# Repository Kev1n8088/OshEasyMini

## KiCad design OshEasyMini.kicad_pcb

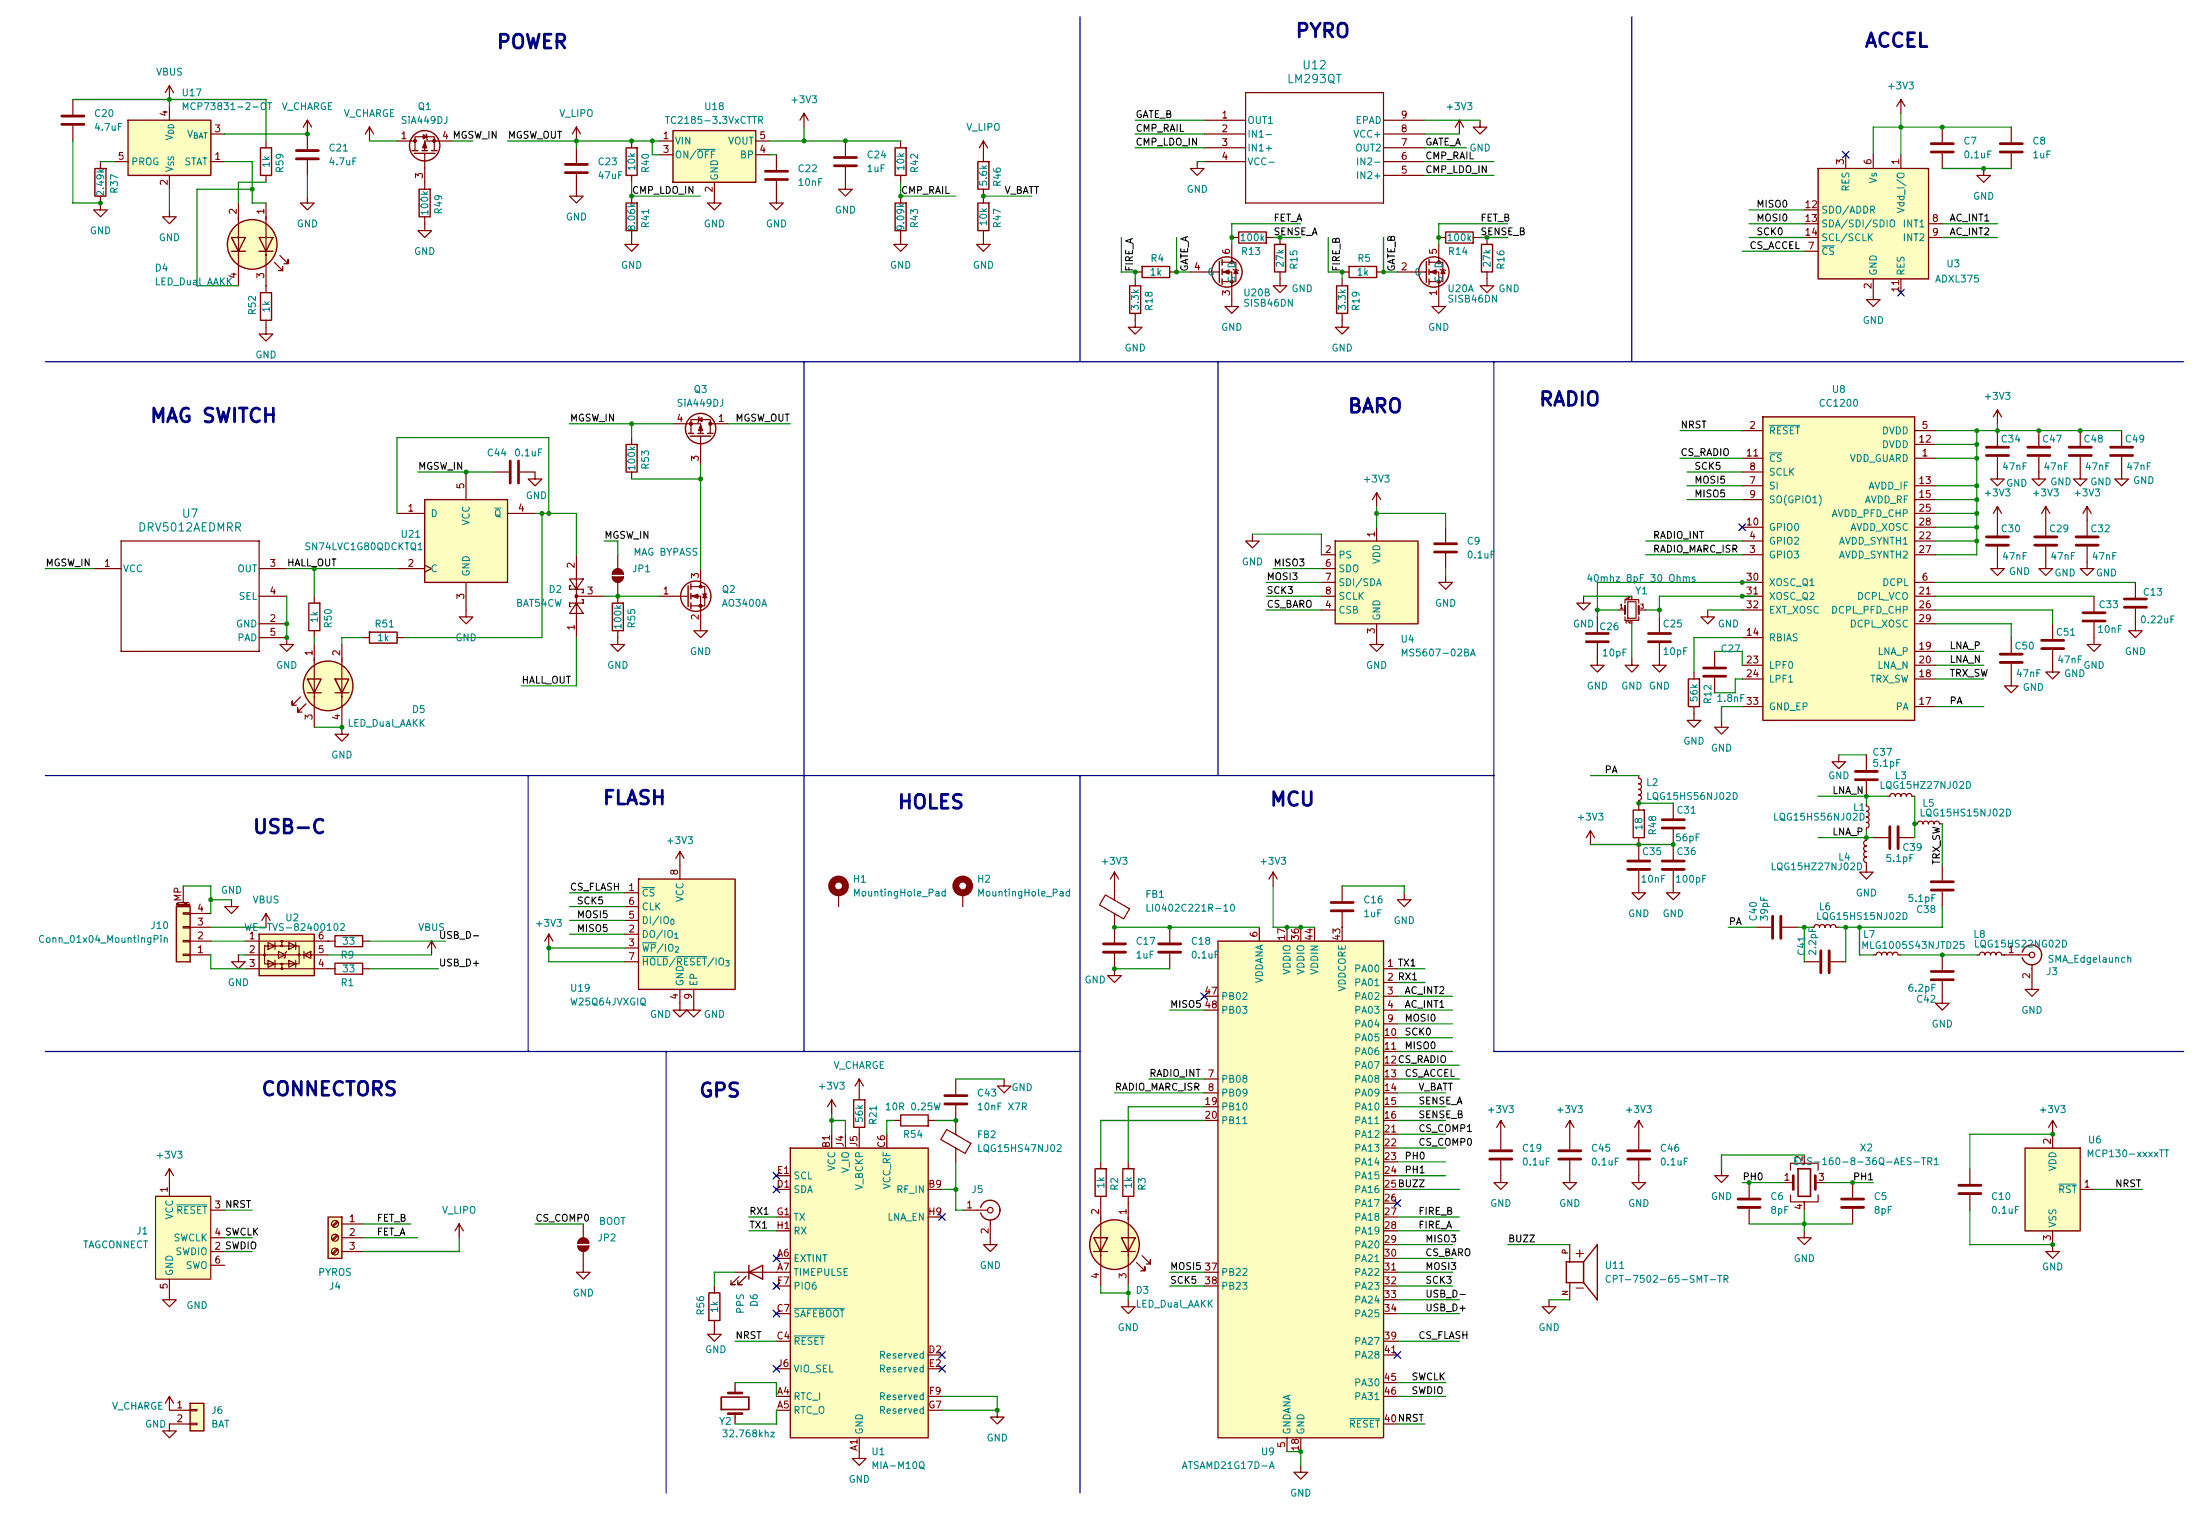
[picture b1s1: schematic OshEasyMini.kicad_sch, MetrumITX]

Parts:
C5, C6: 8pF; C_0402_1005Metric
C7, C9, C10, C18, C19, C44, C45, C46: 0.1uF; C_0402_1005Metric
C8, C16, C17, C24: 1uF; C_0402_1005Metric
C13: 0.22uF; C_0402_1005Metric
C20, C21: 4.7uF; C_0402_1005Metric
C22: 10nF; C_0201_0603Metric
C23: 47uF; C_1206_3216Metric
C25, C26: 10pF; C_0402_1005Metric
C27: 1.8nF; C_0402_1005Metric
C29, C30, C32, C34, C47, C48, C49, C50, C51: 47nF; C_0201_0603Metric
C31: 56pF; C_0402_1005Metric
C33, C35: 10nF; C_0402_1005Metric
C36: 100pF; C_0402_1005Metric
C37, C38, C39: 5.1pF; C_0402_1005Metric
C40: 39pF; C_0402_1005Metric
C41: 2.2pF; C_0402_1005Metric
C42: 6.2pF; C_0402_1005Metric
C43: 10nF X7R; C_0402_1005Metric
D2: BAT54CW; SOT-323_SC-70
D3, D4, D5: LED_Dual_AAKK; DualLED0606
D6: PPS; LED_0402_1005Metric
FB1: LI0402C221R-10; L_0402_1005Metric
FB2: LQG15HS47NJ02; L_0402_1005Metric
H1, H2: MountingHole_Pad; MountingHole_2.7mm_M2.5_DIN965_Pad
J1: TAGCONNECT; Tag-Connect_TC2030-IDC-NL_2x03_P1.27mm_Vertical
J3: SMA_Edgelaunch; SMA_Amphenol_132289_EdgeMount
J4: PYROS; TerminalBlock_Phoenix_MPT-0,5-3-2.54_1x03_P2.54mm_Horizontal
J5: UFL; U.FL_Molex_MCRF_73412-0110_Vertical
J6: BAT; JST_PH_B2B-PH-K_1x02_P2.00mm_Vertical
J10: Conn_01x04_MountingPin; JST_SH_BM04B-SRSS-TB_1x04-1MP_P1.00mm_Vertical
JP1: MAG BYPASS; SolderJumper-2_P1.3mm_Open_TrianglePad1.0x1.5mm
JP2: BOOT; SolderJumper-2_P1.3mm_Open_TrianglePad1.0x1.5mm
L1, L2: LQG15HS56NJ02D; L_0402_1005Metric
L3, L4: LQG15HZ27NJ02D; L_0402_1005Metric
L5, L6: LQG15HS15NJ02D; L_0402_1005Metric
L7: MLG1005S43NJTD25; L_0402_1005Metric
L8: LQG15HS22NG02D; L_0402_1005Metric
Q1, Q3: SiA449DJ; Vishay_PowerPAK_SC70-6L_Single
Q2: AO3400A; SOT-23
R1, R9: 33; R_0201_0603Metric
R2, R3, R4, R5, R50, R51, R52, R56, R59: 1k; R_0201_0603Metric
R12, R21: 56k; R_0402_1005Metric
R13, R14: 100k; R_0402_1005Metric
R15, R16: 27k; R_0402_1005Metric
R18, R19: 3.3k; R_0402_1005Metric
R37: 2.49k; R_0402_1005Metric
R40, R42, R47: 10k; R_0201_0603Metric
R41: 8.06k; R_0201_0603Metric
R43: 9.09k; R_0201_0603Metric
R46: 5.6k; R_0201_0603Metric
R48: 18; R_0402_1005Metric
R49, R53, R55: 100k; R_0201_0603Metric
R54: 10R 0.25W; R_0402_1005Metric
U1: MIA-M10Q; ublox_LGA-53_4.5x4.5mm_Layout9x9_P0.5mm
U2: WE-TVS-82400102; SOT-23-6
U3: ADXL375; LGA-14_3x5mm_P0.8mm_LayoutBorder1x6y
U4: MS5607-02BA; LGA-8_3x5mm_P1.25mm
U6: MCP130-xxxxTT; SOT-23
U7: DRV5012AEDMRR; Texas_X2SON-4-1EP_1.1x1.4mm_P0.5mm_EP0.8x0.6mm
U8: CC1200; QFN-32-1EP_5x5mm_P0.5mm_EP3.45x3.45mm
U9: ATSAMD21G17D-A; TQFP-48_7x7mm_P0.5mm
U11: CPT-7502-65-SMT-TR; XDCR_CPT-7502-65-SMT-TR; PARTREV 1.0
U12: LM293QT; DFN-8-1EP_2x2mm_P0.5mm_EP0.9x1.6mm
U17: MCP73831-2-OT; SOT-23-5
U18: TC2185-3.3VxCTTR; SOT-23-5
U19: W25Q64JVXGIQ; DFN_XGIQ TR_WIN
U20: SISB46DN; PowerPak1212-8-Dual
U21: SN74LVC1G80QDCKTQ1; SOT-353_SC-70-5
X2: ECS-160-8-36Q-AES-TR1; Crystal_SMD_2520-4Pin_2.5x2.0mm
Y1: 40mhz 8pF 30 Ohms; Crystal_SMD_Abracon_ABM10-4Pin_2.5x2.0mm
Y2: 32.768khz; Crystal_SMD_MicroCrystal_CM9V-T1A-2Pin_1.6x1.0mm

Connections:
+3V3: C7.2, C8.2, C9.2, C10.2, C19.2, C24.2, C29.2, C30.2, C31.1, C32.2, C34.2, C35.2, C36.2, C45.2, C46.2, C47.2, C48.2, C49.2, FB1.2, J1.1 (VCC), R42.2, R48.1, U1.B1 (VCC), U1.J4 (V_IO), U3.1 (Vdd_I/O), U3.6 (Vs), U4.1 (VDD), U6.2 (VDD), U8.1 (VDD_GUARD), U8.5 (DVDD), U8.12 (DVDD), U8.13 (AVDD_IF), U8.15 (AVDD_RF), U8.22 (AVDD_SYNTH1), U8.25 (AVDD_PFD_CHP), U8.27 (AVDD_SYNTH2), U8.28 (AVDD_XOSC), U9.17 (VDDIO), U9.36 (VDDIO), U9.44 (VDDIN), U12.8 (VCC+), U18.5 (VOUT), U19.3 (~WP/IO_{2}), U19.7 (~HOLD/~RESET/IO_{3}), U19.8 (VCC)
/AC_INT1: U3.8 (INT1), U9.4 (PA03)
/AC_INT2: U3.9 (INT2), U9.3 (PA02)
/BUZZ: U9.25 (PA16), U11.P
/CMP_LDO_IN: R40.1, R41.2, U12.3 (IN1+), U12.5 (IN2+)
/CMP_RAIL: R42.1, R43.2, U12.2 (IN1-), U12.6 (IN2-)
/CS_ACCEL: U3.7 (~CS), U9.13 (PA08)
/CS_BARO: U4.4 (CSB), U4.5 (CSB), U9.30 (PA21)
/CS_COMP0: JP2.2 (B), U9.22 (PA13)
/CS_COMP1: U9.21 (PA12)
/CS_FLASH: U9.39 (PA27), U19.1 (~CS)
/CS_RADIO: U8.11 (~CS), U9.12 (PA07)
/FET_A: J4.2, R13.1, U20.6 (D)
/FET_B: J4.1, R14.1, U20.5 (D)
/FIRE_A: R4.2, R18.2, U9.28 (PA19)
/FIRE_B: R5.2, R19.2, U9.27 (PA18)
/GATE_A: R4.1, U12.7 (OUT2), U20.4 (G)
/GATE_B: R5.1, U12.1 (OUT1), U20.2 (G)
/HALL_OUT: D2.1, R50.2, U7.3 (OUT), U21.2 (C)
/LNA_N: C37.1, L1.1, L3.1, U8.20 (LNA_N)
/LNA_P: C39.2, L1.2, L4.2, U8.19 (LNA_P)
/MGSW_IN: C44.2, JP1.2 (B), Q1.4 (S), Q3.4 (S), R53.2, U7.1 (VCC), U21.5 (VCC)
/MISO0: U3.12 (SDO/ADDR), U9.11 (PA06)
/MISO3: U4.6 (SDO), U9.29 (PA20)
/MISO5: U8.9 (SO(GPIO1)), U9.48 (PB03), U19.2 (DO/IO_{1})
/MOSI0: U3.13 (SDA/SDI/SDIO), U9.9 (PA04)
/MOSI3: U4.7 (SDI/SDA), U9.31 (PA22)
/MOSI5: U8.7 (SI), U9.37 (PB22), U19.5 (DI/IO_{0})
/NRST: J1.3 (~RESET), U1.C4 (~RESET), U6.1 (~RST), U8.2 (~RESET), U9.40 (~RESET)
/PA: C40.2, L2.1, U8.17 (PA)
/PH0: C6.2, U9.23 (PA14), X2.1
/PH1: C5.2, U9.24 (PA15), X2.3
/RADIO_INT: U8.4 (GPIO2), U9.7 (PB08)
/RADIO_MARC_ISR: U8.3 (GPIO3), U9.8 (PB09)
/RX1: U1.G1 (TX), U9.2 (PA01)
/SCK0: U3.14 (SCL/SCLK), U9.10 (PA05)
/SCK3: U4.8 (SCLK), U9.32 (PA23)
/SCK5: U8.8 (SCLK), U9.38 (PB23), U19.6 (CLK)
/SENSE_A: R13.2, R15.2, U9.15 (PA10)
/SENSE_B: R14.2, R16.2, U9.16 (PA11)
/SWCLK: J1.4 (SWCLK), U9.45 (PA30)
/SWDIO: J1.2 (SWDIO), U9.46 (PA31)
/TRX_SW: C38.1, L5.2, U8.18 (TRX_SW)
/TX1: U1.H1 (RX), U9.1 (PA00)
/USB_D+: R1.2, U9.34 (PA25)
/USB_D-: R9.2, U9.33 (PA24)
/V_BATT: R46.1, R47.2, U9.14 (PA09)
GND: C5.1, C6.1, C7.1, C8.1, C9.1, C10.1, C13.1, C16.2, C17.1, C18.1, C19.1, C20.1, C21.1, C22.1, C23.1, C24.1, C25.1, C26.1, C29.1, C30.1, C32.1, C33.1, C34.1, C35.1, C36.1, C37.2, C42.2, C43.2, C44.1, C45.1, C46.1, C47.1, C48.1, C49.1, C50.1, C51.1, D3.3 (K1), D3.4 (K2), D5.3 (K1), D5.4 (K2), J1.5 (GND), J3.2 (Ext), J5.2 (Ext), J6.2, J10.4, J10.MP (MountPin), JP2.1 (A), L4.1, Q2.2 (S), R12.1, R15.1, R16.1, R18.1, R19.1, R37.1, R41.1, R43.1, R47.1, R49.1, R52.2, R55.1, R56.2, U1.A1 (GND), U1.A2 (GND), U1.A3 (GND), U1.A8 (GND), U1.A9 (GND), U1.B2 (GND), U1.B8 (GND), U1.C3 (GND), U1.C9 (GND), U1.E3 (GND), U1.E4 (GND), U1.E9 (GND), U1.F1 (GND), U1.F3 (GND), U1.F4 (GND), U1.F9 (Reserved), U1.G3 (GND), U1.G4 (GND), U1.G5 (GND), U1.G6 (GND), U1.G7 (Reserved), U1.H8 (GND), U1.J8 (GND), U1.J9 (GND), U2.2, U3.2 (GND), U3.4 (GND), U3.5 (GND), U4.2 (PS), U4.3 (GND), U6.3 (VSS), U7.2 (GND), U7.4 (SEL), U7.5 (PAD), U8.32 (EXT_XOSC), U8.33 (GND_EP), U9.5 (GNDANA), U9.18 (GND), U9.35 (GND), U9.42 (GND), U11.N, U12.4 (VCC-), U12.9 (EPAD), U17.2 (V_{SS}), U18.2 (GND), U19.4 (GND), U19.9 (EP), U20.1 (S), U20.3 (S), U21.3 (GND), X2.2, X2.4, Y1.2, Y1.4; also elsewhere on the board
unnamed: C31.2, L2.2, R48.2
unnamed: C38.2, C41.1, L6.2, L7.1
unnamed: C39.1, L3.2, L5.1
unnamed: C40.1, C41.2, L6.1
unnamed: C42.1, L7.2, L8.1
unnamed: C43.1, FB2.2, R54.2
unnamed: D3.1 (A1), R3.1
unnamed: D3.2 (A2), R2.1
unnamed: D4.1 (A1), D4.4 (K2), U17.1 (STAT)
unnamed: D4.2 (A2), R59.1
unnamed: D4.3 (K1), R52.1
unnamed: D5.1 (A1), R50.1
unnamed: D5.2 (A2), R51.2
unnamed: D6.2 (A), U1.A7 (TIMEPULSE)
unnamed: D6.1 (K), R56.1
unnamed: J3.1 (In), L8.2
unnamed: FB2.1, J5.1 (In), U1.B9 (RF_IN)
unnamed: J10.1, U2.3
unnamed: J10.2, U2.1
unnamed: D2.3, JP1.1 (A), Q2.1 (G), R55.2
unnamed: Q1.3 (G), R49.2
unnamed: Q2.3 (D), Q3.3 (G), R53.1
unnamed: R1.1, U2.4
unnamed: R9.1, U2.6
unnamed: U1.A4 (RTC_I), Y2.2
unnamed: U1.A5 (RTC_O), Y2.1
unnamed: R54.1, U1.C6 (VCC_RF)
unnamed: R21.1, U1.J5 (V_BCKP)
unnamed: C13.2, U8.6 (DCPL)
unnamed: C51.2, U8.26 (DCPL_PFD_CHP)
unnamed: C33.2, U8.21 (DCPL_VCO)
unnamed: C50.2, U8.29 (DCPL_XOSC)
unnamed: C27.2, U8.23 (LPF0)
unnamed: C27.1, U8.24 (LPF1)
unnamed: R12.2, U8.14 (RBIAS)
unnamed: C26.2, U8.30 (XOSC_Q1), Y1.1
unnamed: C25.2, U8.31 (XOSC_Q2), Y1.3
unnamed: R3.2, U9.19 (PB10)
unnamed: R2.2, U9.20 (PB11)
unnamed: C17.2, C18.2, FB1.1, U9.6 (VDDANA)
unnamed: C16.1, U9.43 (VDDCORE)
unnamed: R37.2, U17.5 (PROG)
unnamed: C22.2, U18.4 (BP)
unnamed: D2.2, R51.1, U21.1 (D), U21.4 (~Q)
VBUS: C20.2, J10.3, R59.2, U2.5, U17.4 (V_{DD})
V_CHARGE: C21.2, J6.1, Q1.1 (D), R21.2, U17.3 (V_{BAT})
V_LIPO: C23.2, J4.3, Q3.1 (D), R40.2, R46.2, U18.1 (VIN), U18.3 (ON/~OFF)

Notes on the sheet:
FLASH
PYRO
MCU
USB-C
ACCEL
RADIO
BARO
CONNECTORS
GPS
MAG SWITCH
POWER
HOLES

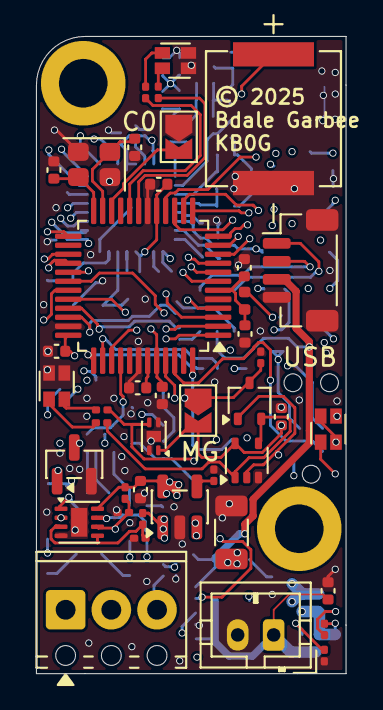
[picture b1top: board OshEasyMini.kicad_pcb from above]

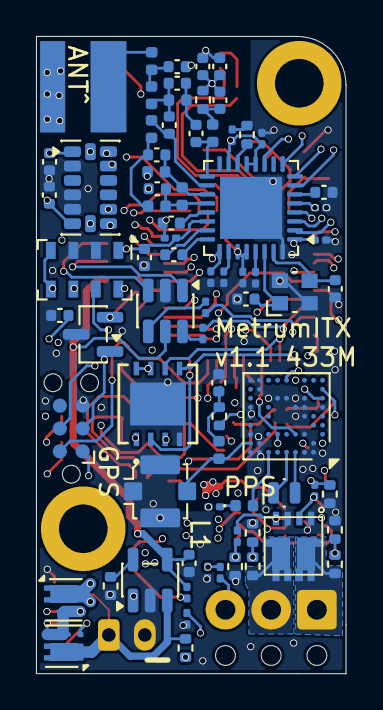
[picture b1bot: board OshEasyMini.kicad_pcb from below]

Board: 6 copper layers, 17.2 x 35.4 mm, 120 parts (76 on the bottom side), 94 nets.

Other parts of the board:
J3#2: SMA_Edgelaunch; SMA_Amphenol_132289_EdgeMount

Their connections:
GND: J3#2.1 (In); also elsewhere on the board

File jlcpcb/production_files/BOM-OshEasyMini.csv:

Comment,Designator,Footprint,LCSC,Quantity
0.1uF,"C10,C18,C19,C44,C45,C46,C7,C9",C_0402_1005Metric,C1525,8
0.22uF,C13,C_0402_1005Metric,C16772,1
1.8nF,C27,C_0402_1005Metric,C107024,1
100k,"R49,R53,R55",R_0201_0603Metric,C106224,3
100k,"R13,R14",R_0402_1005Metric,C25092,2
100pF,C36,C_0402_1005Metric,C1546,1
10R 0.25W,R54,R_0402_1005Metric,C25077,1
10k,"R40,R42,R47",R_0201_0603Metric,C106225,3
10nF,"C33,C35",C_0402_1005Metric,C15195,2
10nF,C22,C_0201_0603Metric,C85930,1
10nF X7R,C43,C_0402_1005Metric,C15195,1
10pF,"C25,C26",C_0402_1005Metric,C32949,2
18,R48,R_0402_1005Metric,C25084,1
1k,"R2,R3,R4,R5,R50,R51,R52,R56,R59",R_0201_0603Metric,C138165,9
1uF,"C16,C17,C24,C8",C_0402_1005Metric,C52923,4
2.2pF,C41,C_0402_1005Metric,C88887,1
2.49k,R37,R_0402_1005Metric,C145071,1
27k,"R15,R16",R_0402_1005Metric,C138022,2
3.3k,"R18,R19",R_0402_1005Metric,C25890,2
32.768khz,Y2,Crystal_SMD_MicroCrystal_CM9V-T1A-2Pin_1.6x1.0mm,C179633,1
39pF,C40,C_0402_1005Metric,C327068,1
4.7uF,"C20,C21",C_0402_1005Metric,C23733,2
40mhz 8pF 30 Ohms,Y1,Crystal_SMD_Abracon_ABM10-4Pin_2.5x2.0mm,C2613038,1
47nF,"C29,C30,C32,C34,C47,C48,C49,C50,C51",C_0201_0603Metric,C88917,9
47uF,C23,C_1206_3216Metric,C96123,1
5.1pF,"C37,C38,C39",C_0402_1005Metric,C281761,3
5.6k,R46,R_0201_0603Metric,C138132,1
56k,"R12,R21",R_0402_1005Metric,C114756,2
56pF,C31,C_0402_1005Metric,C162113,1
6.2pF,C42,C_0402_1005Metric,C161332,1
8.06k,R41,R_0201_0603Metric,C327379,1
8pF,"C5,C6",C_0402_1005Metric,C1549,2
9.09k,R43,R_0201_0603Metric,C158315,1
ADXL375,U3,LGA-14_3x5mm_P0.8mm_LayoutBorder1x6y,C579466,1
AO3400A,Q2,SOT-23,C20917,1
ATSAMD21G17D-A,U9,TQFP-48_7x7mm_P0.5mm,C619065,1
BAT54CW,D2,SOT-323_SC-70,C82467,1
CC1200,U8,QFN-32-1EP_5x5mm_P0.5mm_EP3.45x3.45mm,C122881,1
CPT-7502-65-SMT-TR,U11,XDCR_CPT-7502-65-SMT-TR,C25504047,1
Conn_01x04_MountingPin,J10,JST_SH_BM04B-SRSS-TB_1x04-1MP_P1.00mm_Vertical,C160390,1
DRV5012AEDMRR,U7,Texas_X2SON-4-1EP_1.1x1.4mm_P0.5mm_EP0.8x0.6mm,C2655038,1
ECS-160-8-36Q-AES-TR1,X2,Crystal_SMD_2520-4Pin_2.5x2.0mm,C1669787,1
LED_Dual_AAKK,"D3,D4,D5",DualLED0606,C183840,3
LI0402C221R-10,FB1,L_0402_1005Metric,C269768,1
LM293QT,U12,DFN-8-1EP_2x2mm_P0.5mm_EP0.9x1.6mm,C2970217,1
LQG15HS15NJ02D,"L5,L6",L_0402_1005Metric,C86059,2
LQG15HS22NG02D,L8,L_0402_1005Metric,C12670,1
LQG15HS47NJ02,FB2,L_0402_1005Metric,C97998,1
LQG15HS56NJ02D,"L1,L2",L_0402_1005Metric,C162544,2
LQG15HZ27NJ02D,"L3,L4",L_0402_1005Metric,C560069,2
MCP130-xxxxTT,U6,SOT-23,C410526,1
MCP73831-2-OT,U17,SOT-23-5,C14879,1
MIA-M10Q,U1,ublox_LGA-53_4.5x4.5mm_Layout9x9_P0.5mm,C6990279,1
MLG1005S43NJTD25,L7,L_0402_1005Metric,C2042359,1
MS5607-02BA,U4,LGA-8_3x5mm_P1.25mm,C97627,1
PPS,D6,LED_0402_1005Metric,C364550,1
SISB46DN,U20,PowerPak1212-8-Dual,C22366987,1
SN74LVC1G80QDCKTQ1,U21,SOT-353_SC-70-5,C473331,1
SiA449DJ,"Q1,Q3",Vishay_PowerPAK_SC70-6L_Single,C727325,2
TC2185-3.3VxCTTR,U18,SOT-23-5,C2798212,1
UFL,J5,U.FL_Molex_MCRF_73412-0110_Vertical,C277719,1
W25Q64JVXGIQ,U19,DFN_XGIQ TR_WIN,C2940195,1
WE-TVS-82400102,U2,SOT-23-6,C1975330,1
PYROS,J4,"TerminalBlock_Phoenix_MPT-0,5-3-2.54_1x03_P2.54mm_Horizontal",,1
BAT,J6,JST_PH_B2B-PH-K_1x02_P2.00mm_Vertical,,1
33,R9,R_0201_0603Metric,,1
SMA_Edgelaunch,J3,SMA_Amphenol_132289_EdgeMount,,1
33,R1,R_0201_0603Metric,,1

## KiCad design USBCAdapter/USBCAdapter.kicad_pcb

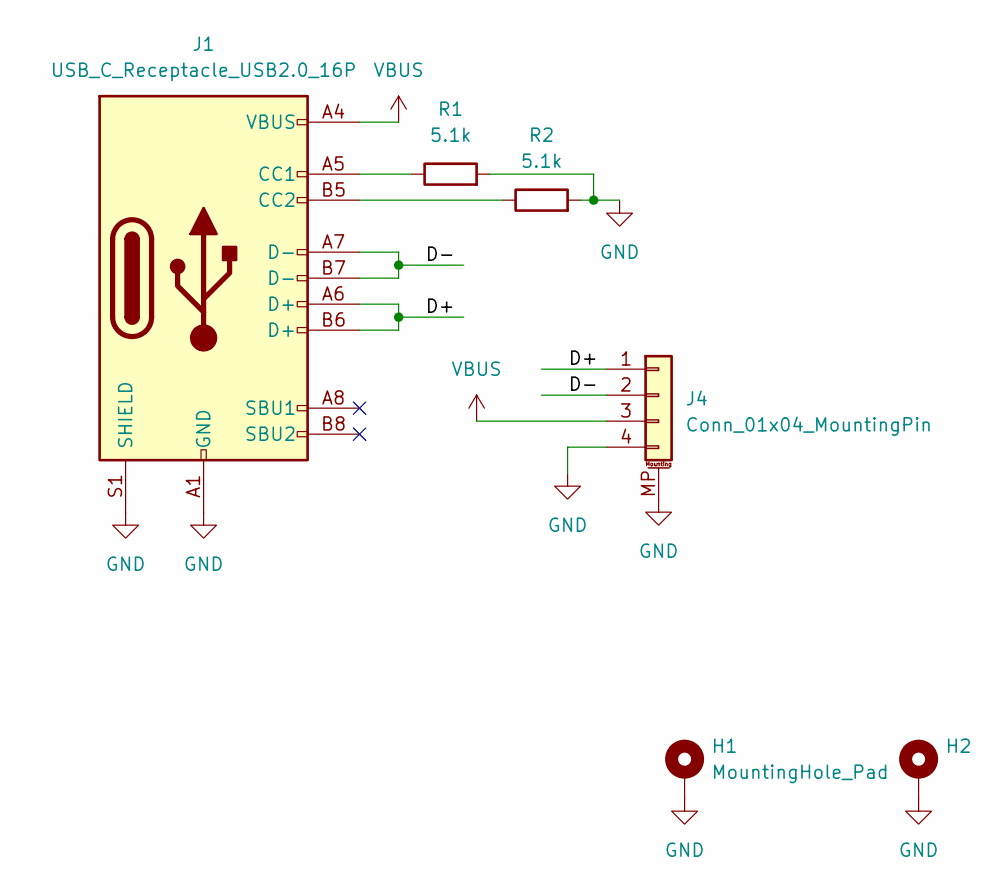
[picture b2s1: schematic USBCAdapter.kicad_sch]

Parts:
H1, H2: MountingHole_Pad; MountingHole_2.7mm_M2.5_DIN965_Pad
J1: USB_C_Receptacle_USB2.0_16P; USB_C_Receptacle_G-Switch_GT-USB-7010ASV
J4: Conn_01x04_MountingPin; JST_SH_SM04B-SRSS-TB_1x04-1MP_P1.00mm_Horizontal
R1, R2: 5.1k; R_0402_1005Metric

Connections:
/D+: J1.A6 (D+), J1.B6 (D+), J4.1
/D-: J1.A7 (D-), J1.B7 (D-), J4.2
GND: H1.1, H2.1, J1.A1 (GND), J1.A12 (GND), J1.B1 (GND), J1.B12 (GND), J1.S1 (SHIELD), J4.4, J4.MP (MountPin), R1.2, R2.2
unnamed: J1.A5 (CC1), R1.1
unnamed: J1.B5 (CC2), R2.1
VBUS: J1.A4 (VBUS), J1.A9 (VBUS), J1.B4 (VBUS), J1.B9 (VBUS), J4.3

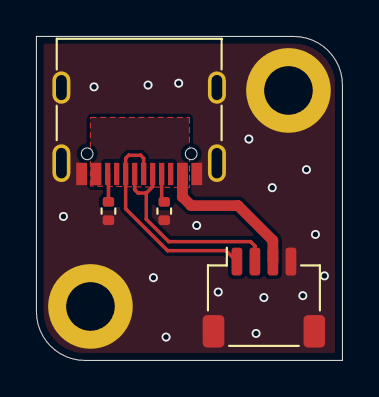
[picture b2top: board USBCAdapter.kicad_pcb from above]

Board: 2 copper layers, 17.0 x 18.0 mm, 6 parts (0 on the bottom side), 6 nets.

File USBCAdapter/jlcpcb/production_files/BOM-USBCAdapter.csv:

Comment,Designator,Footprint,LCSC,Quantity
5.1k,"R1,R2",R_0402_1005Metric,C25905,2
Conn_01x04_MountingPin,J4,JST_SH_SM04B-SRSS-TB_1x04-1MP_P1.00mm_Horizontal,C160404,1
USB_C_Receptacle_USB2.0_16P,J1,USB_C_Receptacle_G-Switch_GT-USB-7010ASV,C2988369,1

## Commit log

2025-11-18 good progress, changed to mia-m10
2025-11-18 all components placed currently routing
2025-11-19 routing done, need to remove SAW and impedance match
2025-11-19 finished usbc daughterboard, next removing charging circuitry onboard
2025-11-19 switched back to onboard charger and the most boring adapter board ever
2025-12-20 ready for final prod after silkscreens
2025-12-20 added silks
2026-02-11 v1 sent for build
2026-02-11 v1.1 revision with capacitor moved to ease in assembly, and added copyright per TAPR
2026-02-20 CRITICAL: GPS UART RX/TX swapped. Fixed.
2026-02-24 some changes
2026-02-24 fixed gnd pad for antenna. Also investigating rf frontend capacitor types

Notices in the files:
OshEasyMini.kicad_pcb:
© 2025
OshEasyMini.kicad_sch:
Copyright 2025 by Bdale Garbee
